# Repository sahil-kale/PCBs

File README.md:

# PCBs

Collection of PCB's designed for personal projects.<br/>
- Schematic and PCB designed in KiCAD

Currently working on: https://github.com/sahil-kale/PCBs/tree/main/PWM_Generator_KiCAD

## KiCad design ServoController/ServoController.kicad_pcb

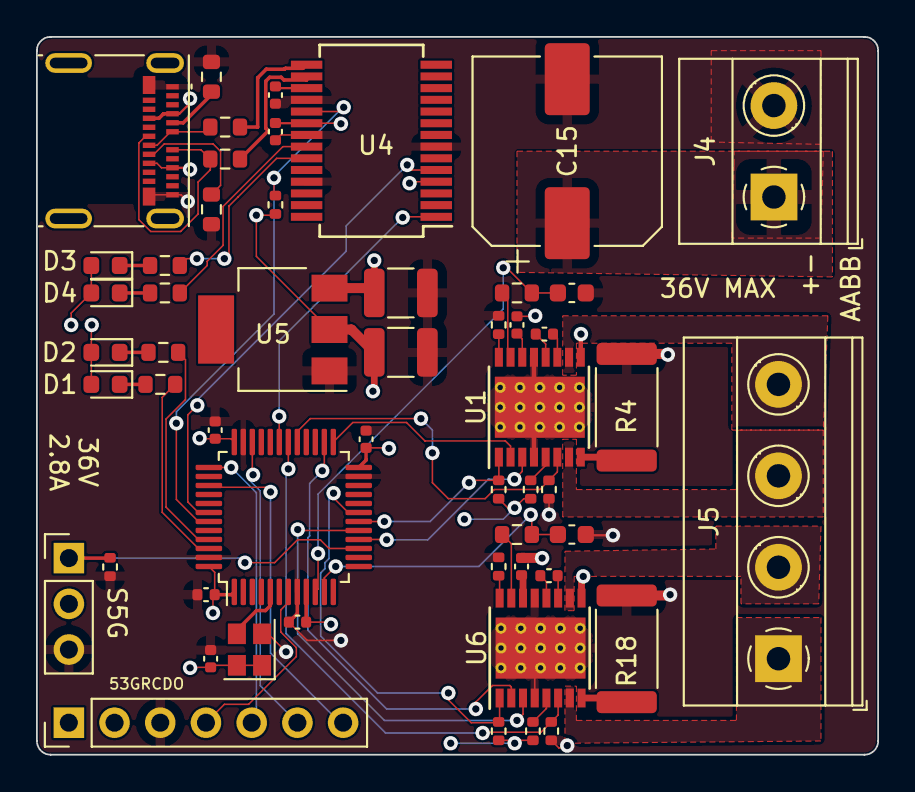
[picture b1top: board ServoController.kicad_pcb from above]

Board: 4 copper layers, 46.7 x 39.9 mm, 53 parts (0 on the bottom side), 56 nets.

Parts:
C1, C2, C13, C14: 0.1uF X7R; C_0402_1005Metric
C3, C4, C5, C6, C7, C8, C11: 0.1uF; C_0402_1005Metric
C9, C10: 22uF; C_1210_3225Metric
C15: 100uF; CP_Elec_10x10
C16, C17: 1000pF; C_0603_1608Metric
D1, D2, D3, D4: LED; LED_0603_1608Metric
J1: Conn_01x03; PinHeader_1x03_P2.54mm_Vertical
J2: Conn_01x07; PinHeader_1x07_P2.54mm_Vertical
J3: USB_C_Receptacle_USB2.0; USB_C_Receptacle_Molex_105450-0101
J4: Conn_01x02; TerminalBlock_Phoenix_MKDS-1,5-2-5.08_1x02_P5.08mm_Horizont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
J5: Conn_01x04; TerminalBlock_Phoenix_MKDS-1,5-4-5.08_1x04_P5.08mm_Horizont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
R1, R2, R3, R5, R12, R15, R16, R17, R19, R20: 10k; R_0402_1005Metric
R4, R18: 200m; R_2512_6332Metric
R6, R7, R13, R14: 470; R_0603_1608Metric
R8, R9: 5.1k; R_0603_1608Metric
R10, R11: 22R; R_0603_1608Metric
R21, R22: 100k; R_0603_1608Metric
U1, U6: DRV8801PWP; HTSSOP-16-1EP_4.4x5mm_P0.65mm_EP3.4x5mm_Mask3x3mm_ThermalVi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
U2: SG-8101CG 40MHz TCHSA; Crystal_SMD_2520-4Pin_2.5x2.0mm
U3: STM32L431CCTx; LQFP-48_7x7mm_P0.5mm
U4: FT232RL; SSOP-28_5.3x10.2mm_P0.65mm
U5: AZ1117-3.3; SOT-223

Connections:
+3V3: C3.1, C4.1, C5.1, C6.1, C7.1, C10.1, D1.2 (A), D2.2 (A), J2.2, R1.1, R5.1, R12.1, R15.1, R19.1, U2.1 (INH), U2.4 (VCC), U3.1 (VBAT), U3.9 (VDDA), U3.24 (VDD), U3.36 (VDD), U3.48 (VDD), U4.4 (VCCIO), U5.2 (VO)
+5V: C9.1, C11.1, D3.2 (A), D4.2 (A), J1.2, J2.1, J3.A4 (VBUS), J3.A9 (VBUS), J3.B4 (VBUS), J3.B9 (VBUS), U4.20 (VCC), U5.3 (VI)
/HBridge1/BRAKE: U3.26 (PB13), U6.2 (MODE1)
/HBridge1/CURR: C17.1, R22.2, U3.11 (PA1)
/HBridge1/DIR: U3.17 (PA7), U6.3 (PHASE)
/HBridge1/EN: R16.1, U3.30 (PA9), U6.6 (ENABLE)
/HBridge1/FAULT: R19.2, U3.19 (PB1), U6.1 (~FAULT)
/HBridge1/OUT+: J5.1, U6.7 (OUT+)
/HBridge1/OUT-: J5.2, U6.10 (OUT-)
/HBridge1/SLEEP: R15.2, U6.5 (~SLEEP)
/HBridge/BRAKE: U1.2 (MODE1), U3.25 (PB12)
/HBridge/CURR: C16.1, R21.2, U3.10 (PA0)
/HBridge/DIR: U1.3 (PHASE), U3.16 (PA6)
/HBridge/EN: R2.1, U1.6 (ENABLE), U3.29 (PA8)
/HBridge/FAULT: R5.2, U1.1 (~FAULT), U3.18 (PB0)
/HBridge/OUT+: J5.3, U1.7 (OUT+)
/HBridge/OUT-: J5.4, U1.10 (OUT-)
/HBridge/SLEEP: R1.2, U1.5 (~SLEEP)
/MCU/NRST: J2.4, U3.7 (NRST)
/MCU/PWM_IN: J1.1, R20.1, U3.15 (PA5)
/MCU/RX: U3.31 (PA10), U4.1 (TXD)
/MCU/SWCLK: J2.5, U3.37 (PA14)
/MCU/SWDIO: J2.6, U3.34 (PA13)
/MCU/SWO: J2.7, U3.39 (PB3)
/MCU/TX: U3.42 (PB6), U4.5 (RXD)
/MCU/UART_RESET: R12.2, U3.43 (PB7), U4.19 (~RESET)
/USB/D+: R11.2, U4.15 (USBD+)
/USB/D-: R10.2, U4.16 (USBD-)
/USB/DN: J3.A7 (D-), J3.B7 (D-), R10.1
/USB/DP: J3.A6 (D+), J3.B6 (D+), R11.1
/USBUART/RXLED: R14.2, U4.22 (CBUS1)
/USBUART/TXLED: R13.2, U4.23 (CBUS0)
GND: C3.2, C4.2, C5.2, C6.2, C7.2, C8.2, C9.2, C10.2, C11.2, C15.2, C16.2, C17.2, J1.3, J2.3, J3.A1 (GND), J3.A12 (GND), J3.B1 (GND), J3.B12 (GND), J4.2, R2.2, R3.2, R4.2, R8.2, R9.2, R16.2, R17.2, R18.2, R20.2, U1.4 (GND), U1.13 (GND), U1.17 (GND(PPAD)), U2.2 (GND), U3.8 (VSSA), U3.23 (VSS), U3.35 (VSS), U3.47 (VSS), U4.7 (GND), U4.18 (GND), U4.21 (GND), U4.25 (AGND), U5.1 (GND), U6.4 (GND), U6.13 (GND), U6.17 (GND(PPAD))
unnamed: C1.1, U1.12 (CP2)
unnamed: C1.2, U1.11 (CP1)
unnamed: C2.1, U1.14 (VCP)
unnamed: C8.1, U4.17 (3V3OUT)
unnamed: C13.1, U6.12 (CP2)
unnamed: C13.2, U6.11 (CP1)
unnamed: C14.1, U6.14 (VCP)
unnamed: D1.1 (K), R6.2
unnamed: D2.1 (K), R7.2
unnamed: D3.1 (K), R13.1
unnamed: D4.1 (K), R14.1
unnamed: J3.A5 (CC1), R9.1
unnamed: J3.B5 (CC2), R8.1
unnamed: R3.1, U1.16 (MODE2)
unnamed: R4.1, U1.8 (SENSE)
unnamed: R6.1, U3.46 (PB9)
unnamed: R7.1, U3.45 (PB8)
unnamed: R17.1, U6.16 (MODE2)
unnamed: R18.1, U6.8 (SENSE)
unnamed: R21.1, U1.15 (VPROPI)
unnamed: R22.1, U6.15 (VPROPI)
unnamed: U2.3 (CLK), U3.5 (PH0)
VBUS: C2.2, C14.2, C15.1, J4.1, U1.9 (VBB), U6.9 (VBB)

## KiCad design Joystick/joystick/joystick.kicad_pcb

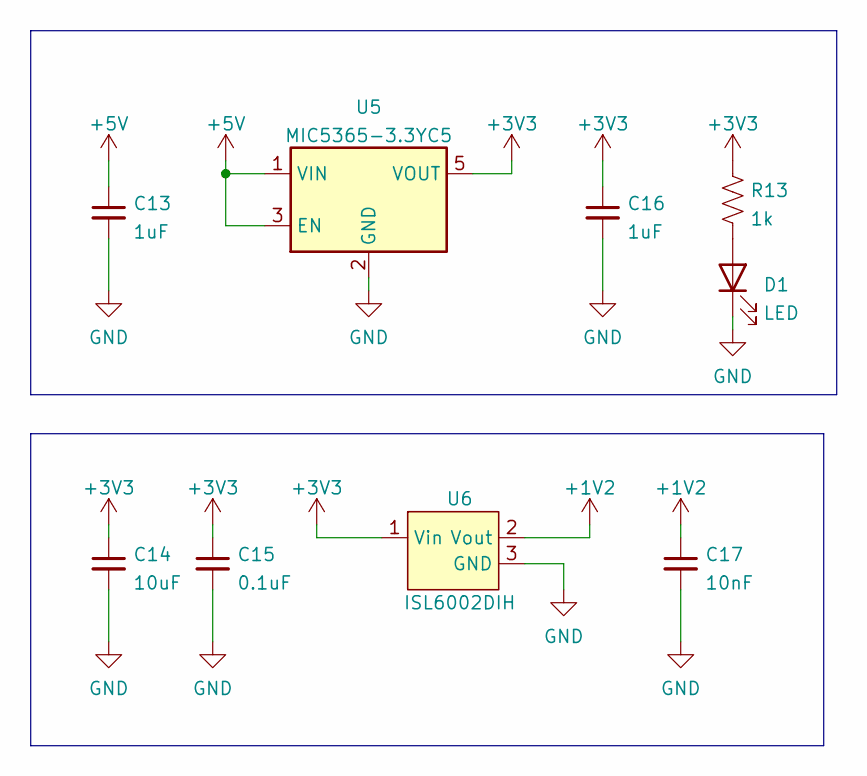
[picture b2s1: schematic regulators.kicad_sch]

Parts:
C13, C16: 1uF; C_0603_1608Metric_Pad1.08x0.95mm_HandSolder; Digikey Part Number 1276-1102-1-ND
C14: 10uF; C_0603_1608Metric_Pad1.08x0.95mm_HandSolder; Digikey Part Number 1276-1119-1-ND
C15: 0.1uF; C_0603_1608Metric_Pad1.08x0.95mm_HandSolder; Digikey Part Number 1276-CL10B104KB8NNNLCT-ND
C17: 10nF; C_0603_1608Metric_Pad1.08x0.95mm_HandSolder; Digikey Part Number 1292-1386-1-ND
D1: LED; LED_0603_1608Metric_Pad1.05x0.95mm_HandSolder; Digikey Part Number 3147-B1931UYG-20D000314U1930CT-ND
R13: 1k; R_0603_1608Metric_Pad0.98x0.95mm_HandSolder; Digikey Part Number RNCP0603FTD1K00CT-ND
U5: MIC5365-3.3YC5; SOT-353_SC-70-5; Digikey Part Number 576-3215-1-ND
U6: ISL6002DIH; SOT-23; Digikey Part Number ISL60002DIH311Z-TKCT-ND

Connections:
+1V2: C17.1, U6.2 (Vout); also elsewhere on the board
+3V3: C14.1, C15.1, C16.1, R13.1, U5.5 (VOUT), U6.1 (Vin); also elsewhere on the board
+5V: C13.1, U5.1 (VIN), U5.3 (EN); also elsewhere on the board
GND: C13.2, C14.2, C15.2, C16.2, C17.2, D1.1 (K), U5.2 (GND), U6.3 (GND); also elsewhere on the board
unnamed: D1.2 (A), R13.2

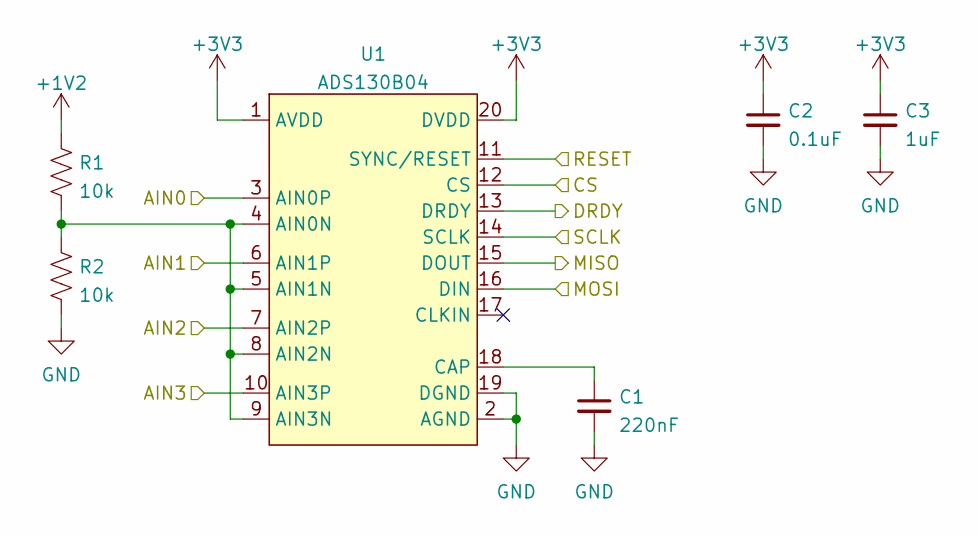
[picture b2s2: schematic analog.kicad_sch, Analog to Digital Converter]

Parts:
C1: 220nF; C_0603_1608Metric_Pad1.08x0.95mm_HandSolder; Digikey Part Number 1292-1419-1-ND
C2: 0.1uF; C_0603_1608Metric_Pad1.08x0.95mm_HandSolder; Digikey Part Number 1276-CL10B104KB8NNNLCT-ND
C3: 1uF; C_0603_1608Metric_Pad1.08x0.95mm_HandSolder; Digikey Part Number 1276-1102-1-ND
R1, R2: 10k; R_0603_1608Metric_Pad0.98x0.95mm_HandSolder; Digikey Part Number RNCP0603FTD10K0CT-ND
U1: ADS130B04; TSSOP-20_4.4x6.5mm_P0.65mm; Digikey Part Number 296-ADS130B04QPWRQ1CT-ND

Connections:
+1V2: R1.1; also elsewhere on the board
+3V3: C2.1, C3.1, U1.1 (AVDD), U1.20 (DVDD); also elsewhere on the board
/Analog Interfaces/AIN0: U1.3 (AIN0P); also elsewhere on the board
/Analog Interfaces/AIN1: U1.6 (AIN1P); also elsewhere on the board
/Analog Interfaces/AIN2: U1.7 (AIN2P); also elsewhere on the board
/Analog Interfaces/AIN3: U1.10 (AIN3P); also elsewhere on the board
/Analog Interfaces/CS: U1.12 (CS); also elsewhere on the board
/Analog Interfaces/DRDY: U1.13 (DRDY); also elsewhere on the board
/Analog Interfaces/MISO: U1.15 (DOUT); also elsewhere on the board
/Analog Interfaces/MOSI: U1.16 (DIN); also elsewhere on the board
/Analog Interfaces/RESET: U1.11 (SYNC/RESET); also elsewhere on the board
/Analog Interfaces/SCLK: U1.14 (SCLK); also elsewhere on the board
GND: C1.2, C2.2, C3.2, R2.2, U1.2 (AGND), U1.19 (DGND); also elsewhere on the board
unnamed: C1.1, U1.18 (CAP)
unnamed: R1.2, R2.1, U1.4 (AIN0N), U1.5 (AIN1N), U1.8 (AIN2N), U1.9 (AIN3N)

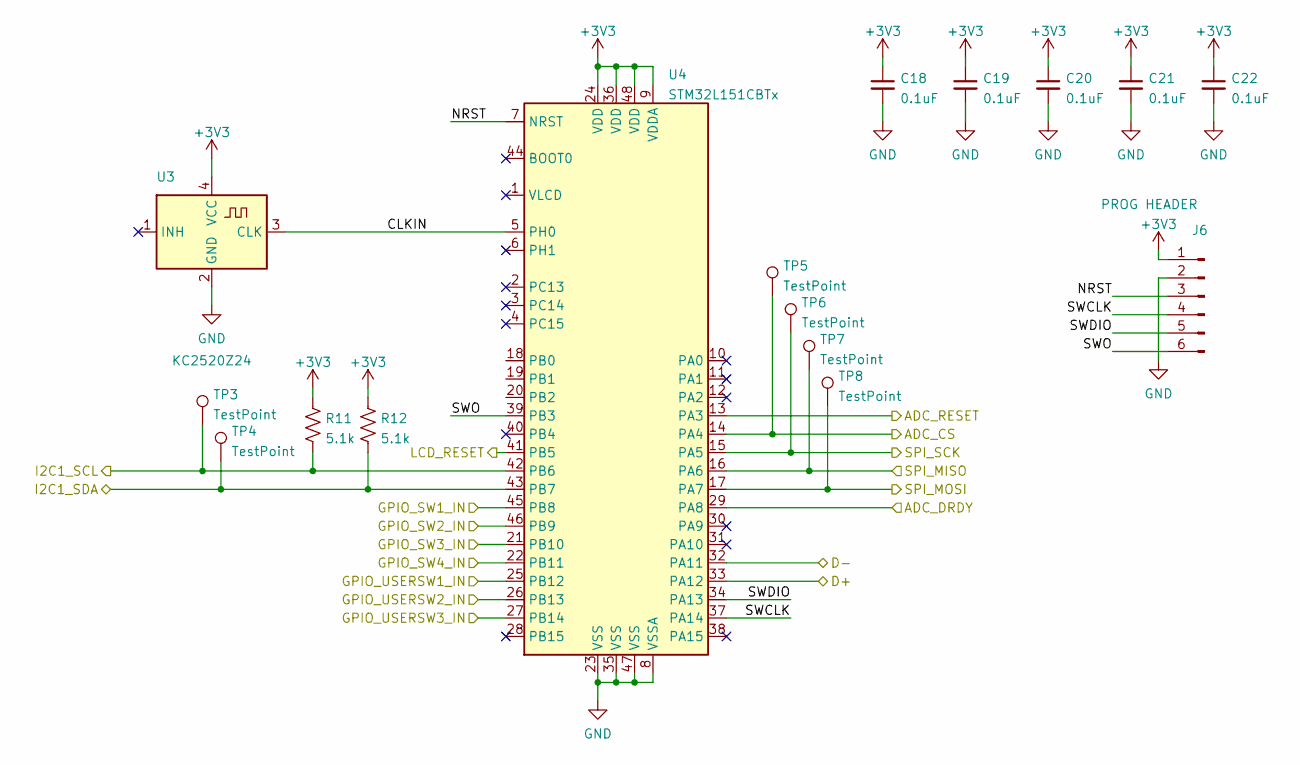
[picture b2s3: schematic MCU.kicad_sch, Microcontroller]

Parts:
C18, C19, C20, C21, C22: 0.1uF; C_0603_1608Metric_Pad1.08x0.95mm_HandSolder
J6: PROG HEADER; PinHeader_1x06_P2.54mm_Vertical
R11, R12: 5.1k; R_0603_1608Metric_Pad0.98x0.95mm_HandSolder; Digikey Part Number RMCF0603JT5K10CT-ND
TP3, TP4, TP5, TP6, TP7, TP8: TestPoint; TestPoint_Pad_D1.0mm
U3: KC2520Z24; Oscillator_SMD_Kyocera_KC2520Z-4Pin_2.5x2.0mm; Digikey Part Number 478-KC2520Z24.0000C15XXKCT-ND
U4: STM32L151CBTx; LQFP-48_7x7mm_P0.5mm; Digikey Part Number 497-11191-ND

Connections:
+3V3: C18.1, C19.1, C20.1, C21.1, C22.1, J6.1, R11.1, R12.1, U3.4 (VCC), U4.9 (VDDA), U4.24 (VDD), U4.36 (VDD), U4.48 (VDD); also elsewhere on the board
/Analog Interfaces/CS: TP5.1, U4.14 (PA4); also elsewhere on the board
/Analog Interfaces/DRDY: U4.29 (PA8); also elsewhere on the board
/Analog Interfaces/MISO: TP7.1, U4.16 (PA6); also elsewhere on the board
/Analog Interfaces/MOSI: TP8.1, U4.17 (PA7); also elsewhere on the board
/Analog Interfaces/RESET: U4.13 (PA3); also elsewhere on the board
/Analog Interfaces/SCLK: TP6.1, U4.15 (PA5); also elsewhere on the board
/Button Interfaces/SW_1: U4.45 (PB8); also elsewhere on the board
/Button Interfaces/SW_2: U4.46 (PB9); also elsewhere on the board
/Button Interfaces/SW_3: U4.21 (PB10); also elsewhere on the board
/Button Interfaces/SW_4: U4.22 (PB11); also elsewhere on the board
/Button Interfaces/USER_SW_1: U4.25 (PB12); also elsewhere on the board
/Button Interfaces/USER_SW_2: U4.26 (PB13); also elsewhere on the board
/Button Interfaces/USER_SW_3: U4.27 (PB14); also elsewhere on the board
/LCD/RST: U4.41 (PB5); also elsewhere on the board
/LCD/SCL: R11.2, TP3.1, U4.42 (PB6); also elsewhere on the board
/LCD/SDA: R12.2, TP4.1, U4.43 (PB7); also elsewhere on the board
/MCU/CLKIN: U3.3 (CLK), U4.5 (PH0)
/MCU/NRST: J6.3, U4.7 (NRST)
/MCU/SWCLK: J6.4, U4.37 (PA14)
/MCU/SWDIO: J6.5, U4.34 (PA13)
/MCU/SWO: J6.6, U4.39 (PB3)
/USB/D+: U4.33 (PA12); also elsewhere on the board
/USB/D-: U4.32 (PA11); also elsewhere on the board
GND: C18.2, C19.2, C20.2, C21.2, C22.2, J6.2, U3.2 (GND), U4.8 (VSSA), U4.23 (VSS), U4.35 (VSS), U4.47 (VSS); also elsewhere on the board

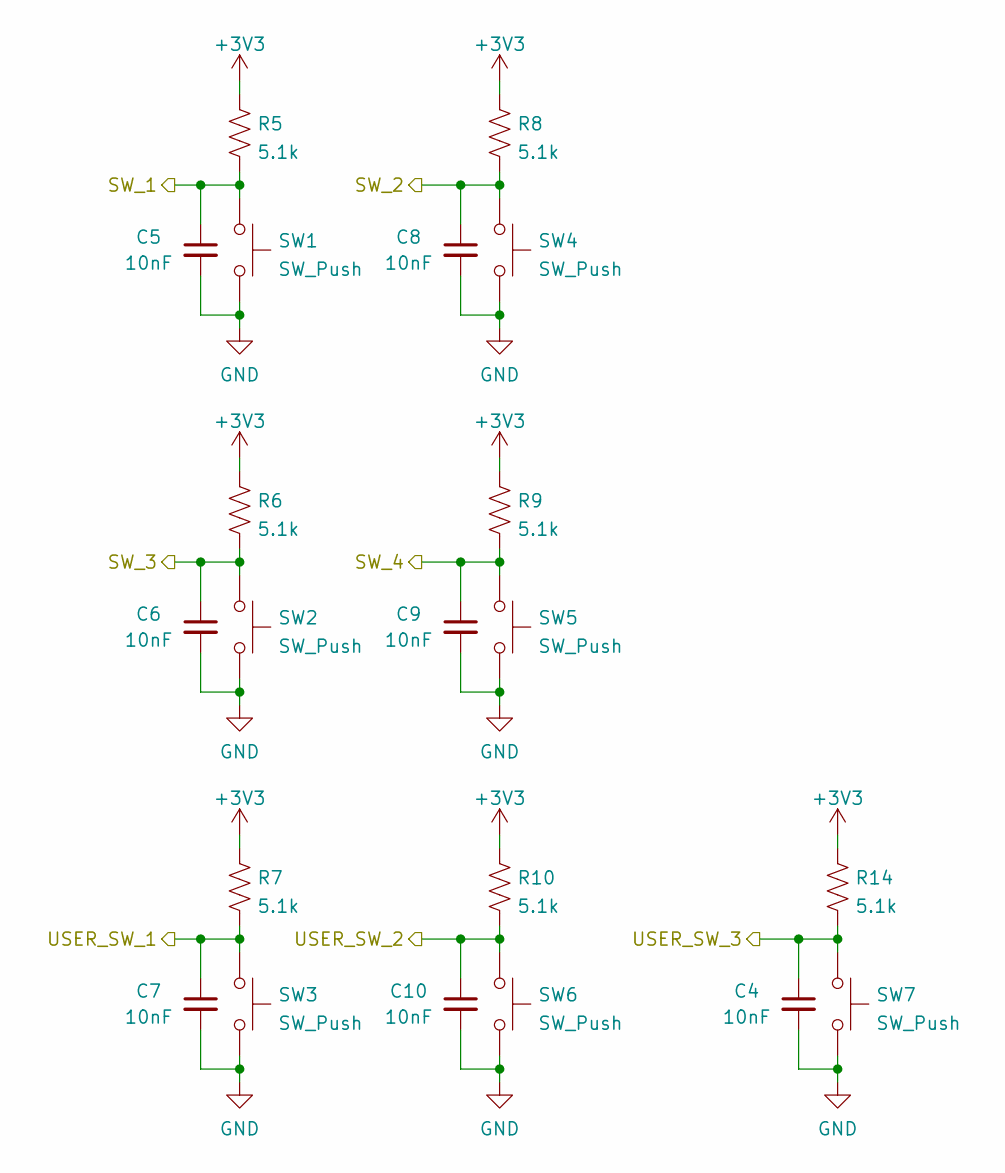
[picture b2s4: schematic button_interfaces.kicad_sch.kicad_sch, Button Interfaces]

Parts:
C4, C5, C6, C7, C8, C9, C10: 10nF; C_0603_1608Metric_Pad1.08x0.95mm_HandSolder; Digikey Part Number 1292-1386-1-ND
R5, R6, R7, R8, R9, R10, R14: 5.1k; R_0603_1608Metric_Pad0.98x0.95mm_HandSolder; Digikey Part Number RMCF0603JT5K10CT-ND
SW1, SW2, SW3, SW4, SW5, SW6, SW7: SW_Push; SW_Push_1P1T_NO_6x6mm_H9.5mm; Digikey Part Number 360-2595-1-ND

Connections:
+3V3: R5.1, R6.1, R7.1, R8.1, R9.1, R10.1, R14.1; also elsewhere on the board
/Button Interfaces/SW_1: C5.1, R5.2, SW1.1; also elsewhere on the board
/Button Interfaces/SW_2: C8.1, R8.2, SW4.1; also elsewhere on the board
/Button Interfaces/SW_3: C6.1, R6.2, SW2.1; also elsewhere on the board
/Button Interfaces/SW_4: C9.1, R9.2, SW5.1; also elsewhere on the board
/Button Interfaces/USER_SW_1: C7.1, R7.2, SW3.1; also elsewhere on the board
/Button Interfaces/USER_SW_2: C10.1, R10.2, SW6.1; also elsewhere on the board
/Button Interfaces/USER_SW_3: C4.1, R14.2, SW7.1; also elsewhere on the board
GND: C4.2, C5.2, C6.2, C7.2, C8.2, C9.2, C10.2, SW1.2, SW2.2, SW3.2, SW4.2, SW5.2, SW6.2, SW7.2; also elsewhere on the board

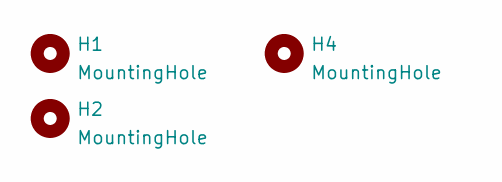
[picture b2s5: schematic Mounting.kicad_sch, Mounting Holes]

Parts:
H1, H2, H4: MountingHole; MountingHole_2.1mm

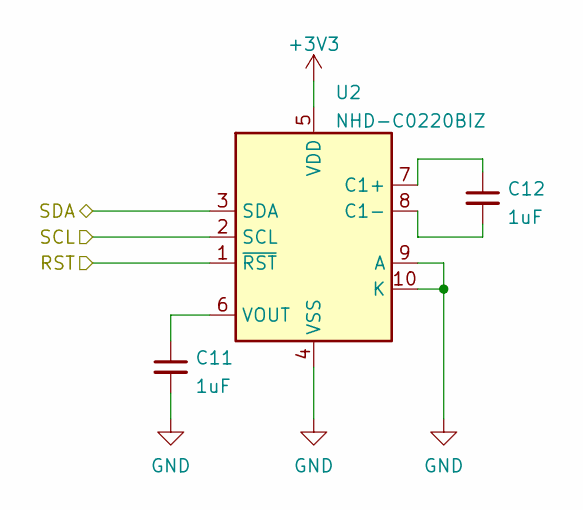
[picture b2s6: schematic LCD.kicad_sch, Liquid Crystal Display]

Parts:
C11, C12: 1uF; C_0603_1608Metric_Pad1.08x0.95mm_HandSolder; Digikey Part Number 1276-1102-1-ND
U2: NHD-C0220BIZ; NHD-C0220BiZ; Digikey Part Number NHD-C0220BIZ-FSW-FBW-3V3M-ND

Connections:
+3V3: U2.5 (VDD); also elsewhere on the board
/LCD/RST: U2.1 (~RST); also elsewhere on the board
/LCD/SCL: U2.2 (SCL); also elsewhere on the board
/LCD/SDA: U2.3 (SDA); also elsewhere on the board
GND: C11.2, U2.4 (VSS), U2.9 (A), U2.10 (K); also elsewhere on the board
unnamed: C11.1, U2.6 (VOUT)
unnamed: C12.1, U2.7 (C1+)
unnamed: C12.2, U2.8 (C1-)

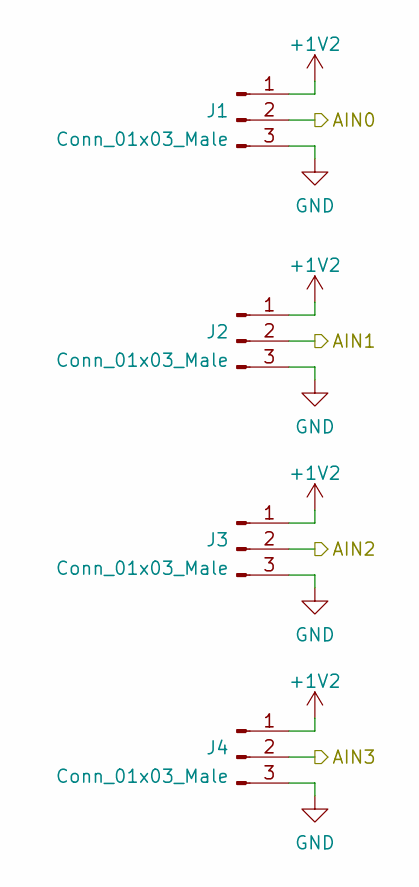
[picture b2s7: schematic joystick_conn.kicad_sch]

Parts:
J1, J2, J3, J4: Conn_01x03_Male; PinHeader_1x03_P2.54mm_Vertical

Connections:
+1V2: J1.1, J2.1, J3.1, J4.1; also elsewhere on the board
/Analog Interfaces/AIN0: J1.2; also elsewhere on the board
/Analog Interfaces/AIN1: J2.2; also elsewhere on the board
/Analog Interfaces/AIN2: J3.2; also elsewhere on the board
/Analog Interfaces/AIN3: J4.2; also elsewhere on the board
GND: J1.3, J2.3, J3.3, J4.3; also elsewhere on the board

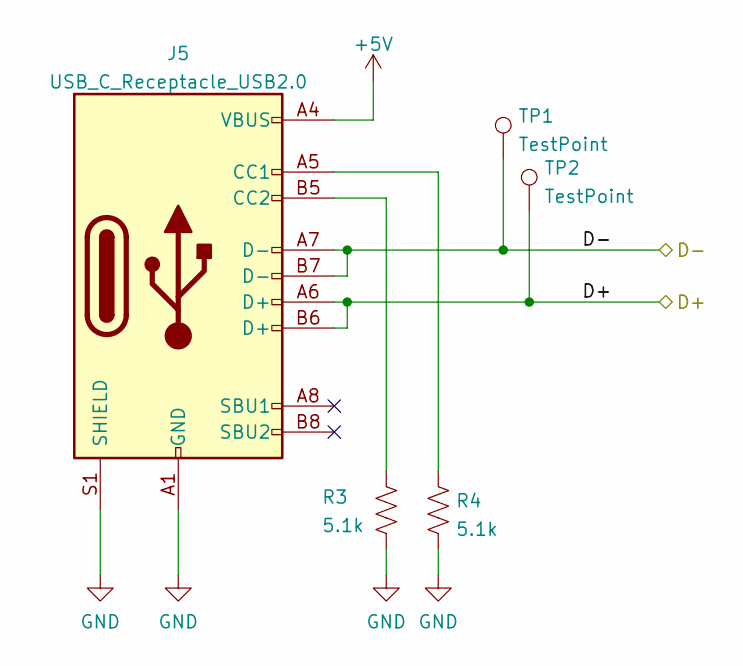
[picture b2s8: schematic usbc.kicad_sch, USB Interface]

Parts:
J5: USB_C_Receptacle_USB2.0; USB_C_Receptacle_JAE_DX07S016JA1R1500; Digikey Part Number 670-DX07S016JA1R1500CT-ND
R3, R4: 5.1k; R_0603_1608Metric_Pad0.98x0.95mm_HandSolder; Digikey Part Number RMCF0603JT5K10CT-ND
TP1, TP2: TestPoint; TestPoint_Pad_D1.0mm

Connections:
+5V: J5.A4 (VBUS), J5.A9 (VBUS), J5.B4 (VBUS), J5.B9 (VBUS); also elsewhere on the board
/USB/D+: J5.A6 (D+), J5.B6 (D+), TP2.1; also elsewhere on the board
/USB/D-: J5.A7 (D-), J5.B7 (D-), TP1.1; also elsewhere on the board
GND: J5.A1 (GND), J5.A12 (GND), J5.B1 (GND), J5.B12 (GND), J5.S1 (SHIELD), R3.2, R4.2; also elsewhere on the board
unnamed: J5.A5 (CC1), R4.1
unnamed: J5.B5 (CC2), R3.1

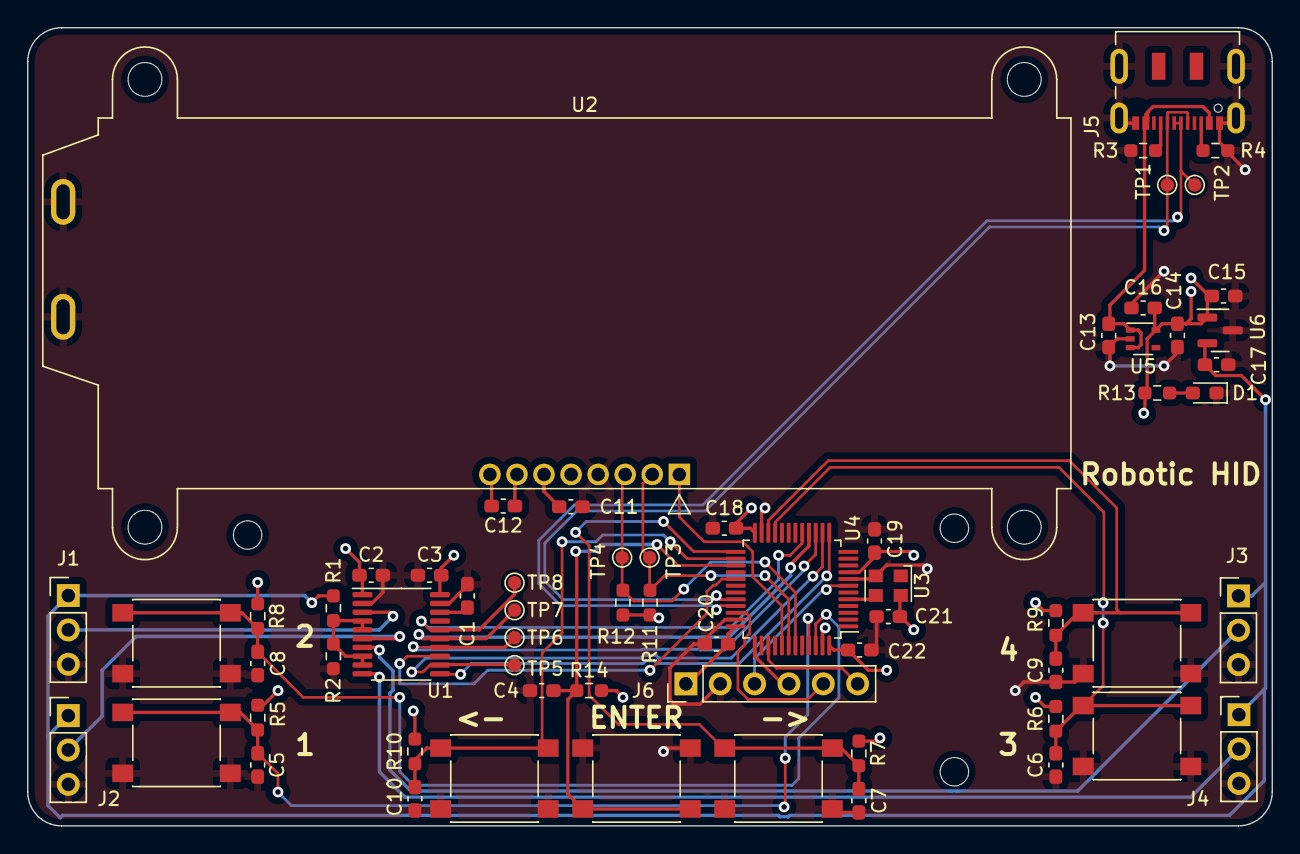
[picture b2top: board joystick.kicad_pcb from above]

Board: 4 copper layers, 92.0 x 59.0 mm, 67 parts (0 on the bottom side), 39 nets.

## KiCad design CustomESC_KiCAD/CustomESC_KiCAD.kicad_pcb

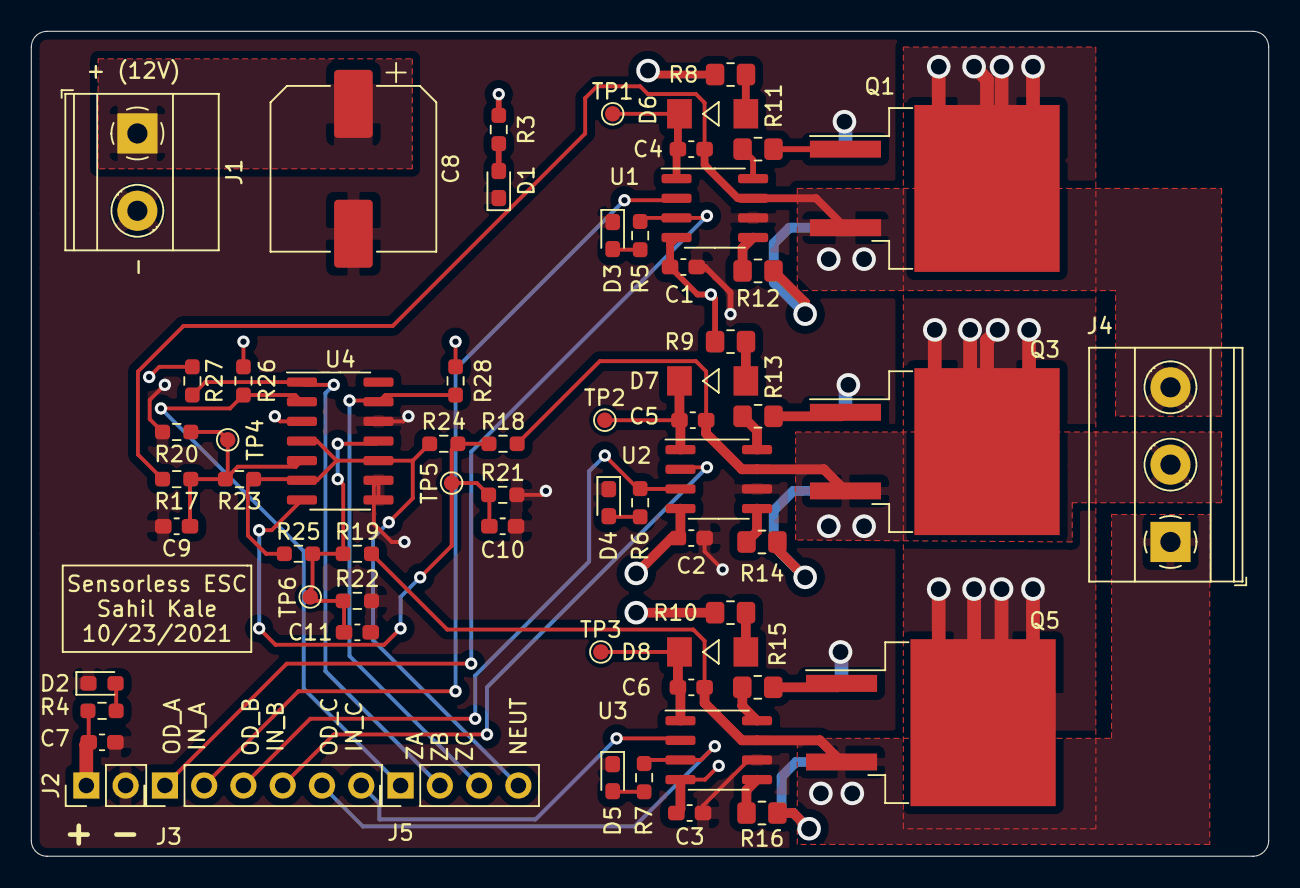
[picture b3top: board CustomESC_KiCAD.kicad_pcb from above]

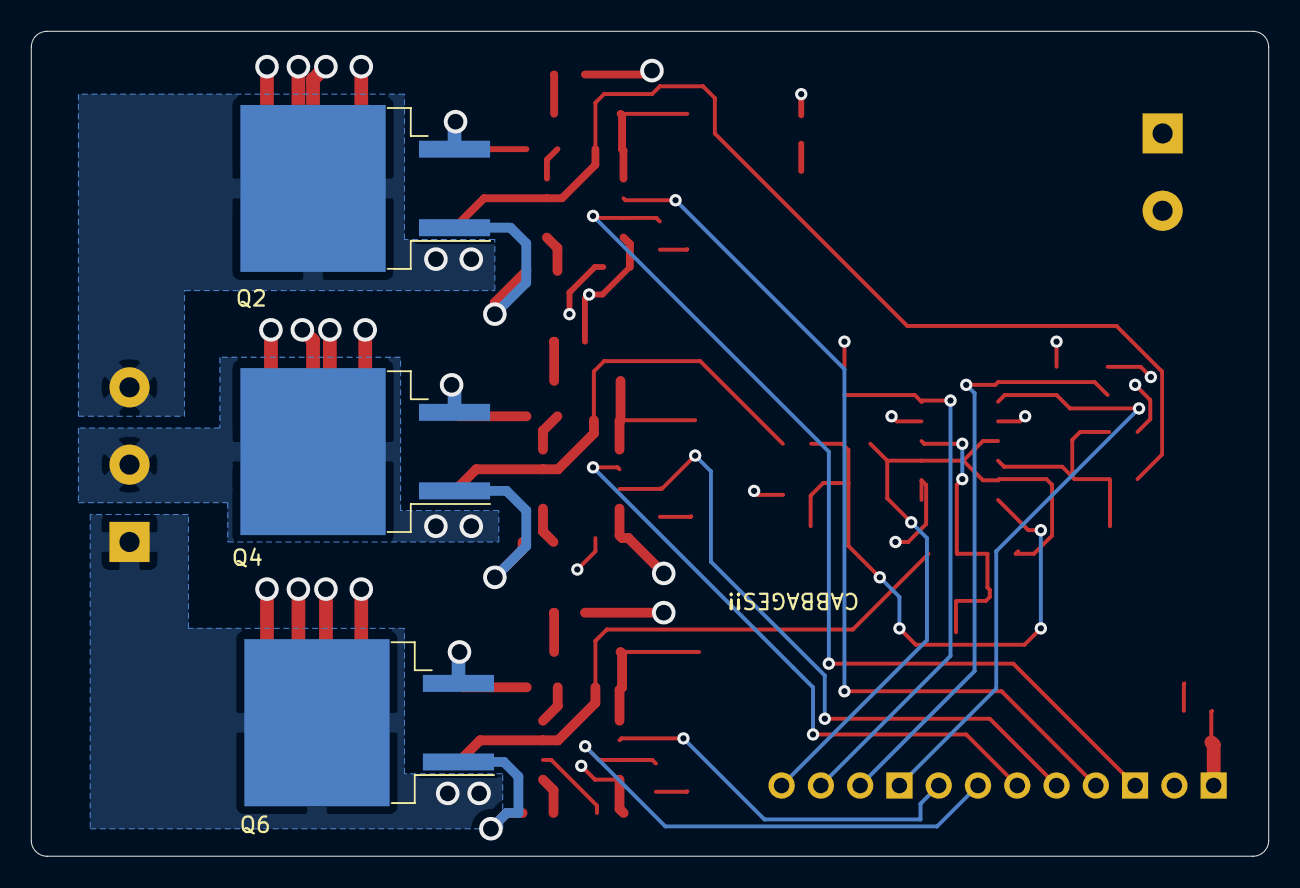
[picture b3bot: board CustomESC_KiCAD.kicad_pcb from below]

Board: 4 copper layers, 80.0 x 53.3 mm, 66 parts (3 on the bottom side), 42 nets.

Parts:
C1, C2, C3: 1uF; C_0603_1608Metric_Pad1.08x0.95mm_HandSolder
C4, C5, C6, C7: 0.1uF; C_0603_1608Metric_Pad1.08x0.95mm_HandSolder
C8: 100uF; CP_Elec_10x10.5
C9, C10, C11: 1nF; C_0603_1608Metric_Pad1.08x0.95mm_HandSolder
D1, D2, D3, D4, D5: LED; LED_0603_1608Metric_Pad1.05x0.95mm_HandSolder
D6, D7, D8: SK53AFL-TP; SK53AFL
J1: Screw_Terminal_01x02; TerminalBlock_Phoenix_MKDS-1,5-2_1x02_P5.00mm_Horizontal
J2: Screw_Terminal_01x02; PinHeader_1x02_P2.54mm_Vertical
J3: Screw_Terminal_01x06; PinHeader_1x06_P2.54mm_Vertical
J4: Screw_Terminal_01x03; TerminalBlock_Phoenix_MKDS-1,5-3_1x03_P5.00mm_Horizontal
J5: Screw_Terminal_01x04; PinHeader_1x04_P2.54mm_Vertical
Q1, Q2, Q3, Q4, Q5, Q6: Q_NMOS_GDS; TO-263-2
R3, R4, R5, R6, R7: 1k; R_0603_1608Metric_Pad0.98x0.95mm_HandSolder
R8, R9, R10, R11, R12, R13, R14, R15, R16: 5.1; R_0805_2012Metric_Pad1.20x1.40mm_HandSolder
R17, R18, R19, R23, R24, R25: 33k; R_0603_1608Metric_Pad0.98x0.95mm_HandSolder
R20, R21, R22, R26, R27, R28: 10k; R_0603_1608Metric_Pad0.98x0.95mm_HandSolder
TP1, TP2, TP3: TP_BST; TestPoint_Pad_D1.0mm
TP4, TP5, TP6: TestPoint; TestPoint_Pad_D1.0mm
U1, U2, U3: ADP3110AKRZ-RL; SOIC-8_3.9x4.9mm_P1.27mm
U4: LM339; SOIC-14_3.9x8.7mm_P1.27mm

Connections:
/BackEMF/BEMFA: C9.1, R17.1, R20.1, R23.2, TP4.1, U4.5
/BackEMF/BEMFB: C10.1, R18.1, R21.1, R24.2, TP5.1, U4.7
/BackEMF/BEMFC: C11.1, R19.1, R22.1, R25.2, TP6.1, U4.11
/IN_A: J3.2, U1.2
/IN_B: J3.4, U2.2
/IN_C: J3.6, U3.2
/OD_A: J3.1, R5.1, U1.3
/OD_B: J3.3, R6.1, U2.3
/OD_C: J3.5, R7.1, U3.3
GND: C1.2, C2.2, C3.2, C7.1, C8.2, C9.2, C10.2, C11.2, D1.1, D2.1, D3.1, D4.1, D5.1, J1.2, J2.2, Q2.3, Q4.3, Q6.3, R20.2, R21.2, R22.2, U1.6, U2.6, U3.6, U4.8, U4.9, U4.12
NEUT: J5.4, R23.1, R24.1, R25.1, U4.4, U4.6, U4.10
unnamed: C4.2, D6.1, TP1.1, U1.1
unnamed: C5.2, D7.1, TP2.1, U2.1
unnamed: C6.2, D8.1, TP3.1, U3.1
unnamed: D1.2, R3.2
unnamed: D2.2, R4.2
unnamed: D3.2, R5.2
unnamed: D4.2, R6.2
unnamed: D5.2, R7.2
unnamed: D6.2, R8.1
unnamed: D7.2, R9.1
unnamed: D8.2, R10.1
unnamed: Q1.1, R11.1
unnamed: Q2.1, R12.1
unnamed: Q3.1, R13.1
unnamed: Q4.1, R14.1
unnamed: Q5.1, R15.1
unnamed: Q6.1, R16.1
unnamed: R11.2, U1.8
unnamed: R12.2, U1.5
unnamed: R13.2, U2.8
unnamed: R14.2, U2.5
unnamed: R15.2, U3.8
unnamed: R16.2, U3.5
PHASEA: C4.1, J4.3, Q1.3, Q2.2, R17.2, U1.7
PHASEB: C5.1, J4.2, Q3.3, Q4.2, R18.2, U2.7
PHASEC: C6.1, J4.1, Q5.3, Q6.2, R19.2, U3.7
VBUS: C1.1, C2.1, C3.1, C8.1, J1.1, Q1.2, Q3.2, Q5.2, R3.1, R8.2, R9.2, R10.2, U1.4, U2.4, U3.4
VCC: C7.2, J2.1, R4.1, R26.1, R27.1, R28.1, U4.3
ZCROSS_A: J5.1, R26.2, U4.2
ZCROSS_B: J5.2, R27.2, U4.1
ZCROSS_C: J5.3, R28.2, U4.13

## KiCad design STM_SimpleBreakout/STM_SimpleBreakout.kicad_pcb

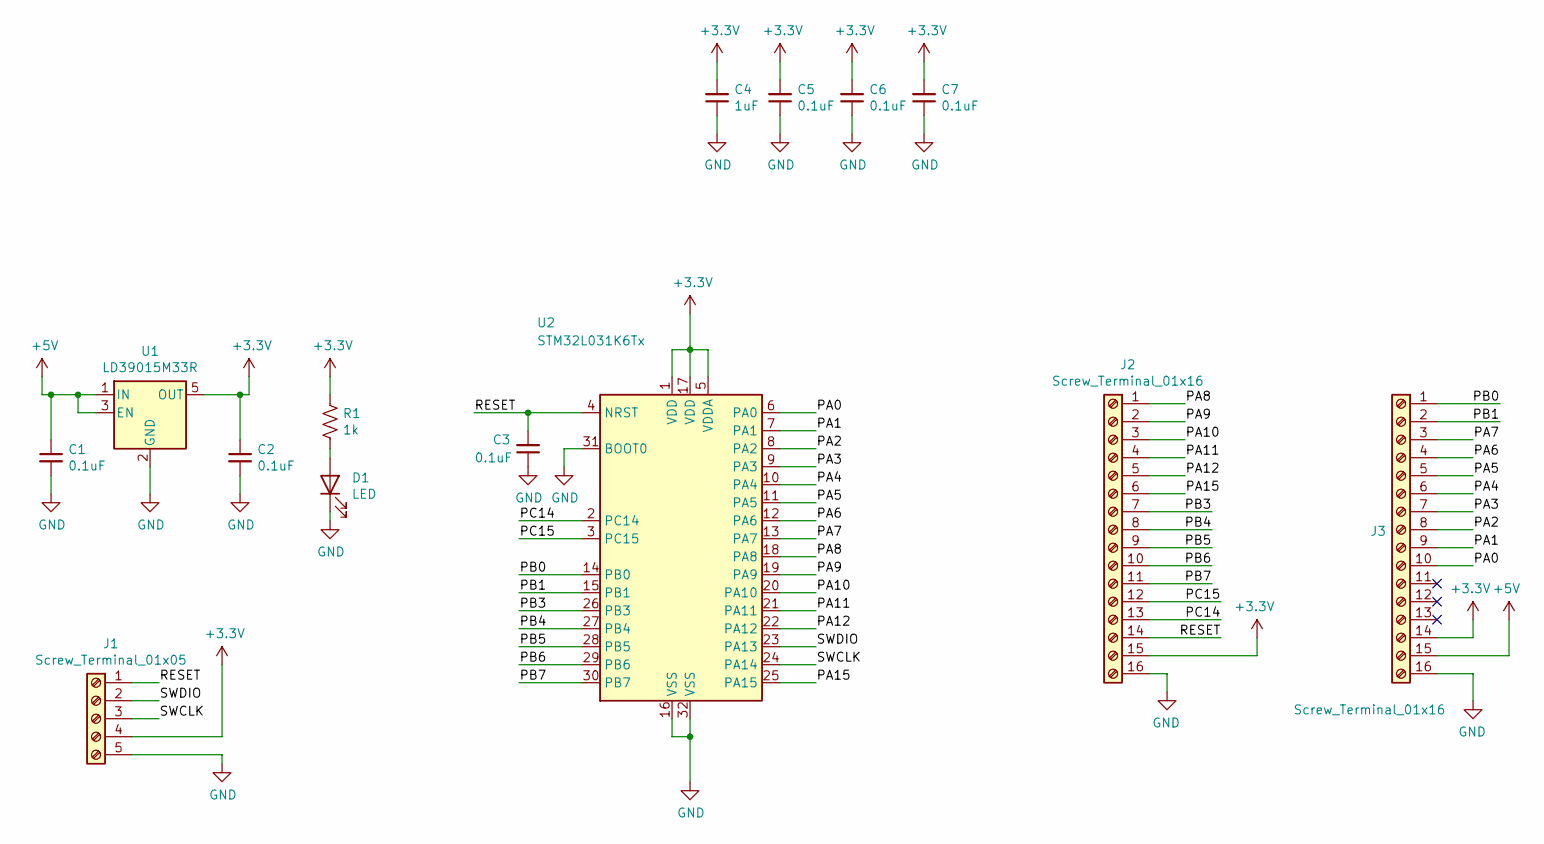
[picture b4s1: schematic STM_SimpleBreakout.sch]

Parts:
C1, C2, C3, C5, C6, C7: 0.1uF; C_0603_1608Metric_Pad1.08x0.95mm_HandSolder; Digikey Part Num 445-7435-1-ND
C4: 1uF; C_0603_1608Metric_Pad1.08x0.95mm_HandSolder; Digikey Part Num 445-7435-1-ND
D1: LED; LED_0603_1608Metric_Pad1.05x0.95mm_HandSolder
J1: Screw_Terminal_01x05; PinHeader_1x05_P2.54mm_Vertical
J2, J3: Screw_Terminal_01x16; PinHeader_1x16_P2.54mm_Vertical
R1: 1k; R_0603_1608Metric_Pad0.98x0.95mm_HandSolder
U1: LD39015M33R; SOT-23-5; Digikey Part Num 497-6979-1-ND
U2: STM32L031K6Tx; LQFP-32_7x7mm_P0.8mm; Digikey Part Num 497-18806-1-ND

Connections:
+3V3: C2.1, C4.2, C5.2, C6.2, C7.2, J1.4, J2.15, J3.14, R1.1, U1.5 (OUT), U2.1 (VDD), U2.5 (VDDA), U2.17 (VDD)
+5V: C1.1, J3.15, U1.1 (IN), U1.3 (EN)
/PA0: J3.10, U2.6 (PA0)
/PA1: J3.9, U2.7 (PA1)
/PA2: J3.8, U2.8 (PA2)
/PA3: J3.7, U2.9 (PA3)
/PA4: J3.6, U2.10 (PA4)
/PA5: J3.5, U2.11 (PA5)
/PA6: J3.4, U2.12 (PA6)
/PA7: J3.3, U2.13 (PA7)
/PA8: J2.1, U2.18 (PA8)
/PA9: J2.2, U2.19 (PA9)
/PA10: J2.3, U2.20 (PA10)
/PA11: J2.4, U2.21 (PA11)
/PA12: J2.5, U2.22 (PA12)
/PA15: J2.6, U2.25 (PA15)
/PB0: J3.1, U2.14 (PB0)
/PB1: J3.2, U2.15 (PB1)
/PB3: J2.7, U2.26 (PB3)
/PB4: J2.8, U2.27 (PB4)
/PB5: J2.9, U2.28 (PB5)
/PB6: J2.10, U2.29 (PB6)
/PB7: J2.11, U2.30 (PB7)
/PC14: J2.13, U2.2 (PC14)
/PC15: J2.12, U2.3 (PC15)
/RESET: C3.2, J1.1, J2.14, U2.4 (NRST)
/SWCLK: J1.3, U2.24 (PA14)
/SWDIO: J1.2, U2.23 (PA13)
GND: C1.2, C2.2, C3.1, C4.1, C5.1, C6.1, C7.1, D1.1 (K), J1.5, J2.16, J3.16, U1.2 (GND), U2.16 (VSS), U2.31 (BOOT0), U2.32 (VSS)
unnamed: D1.2 (A), R1.2

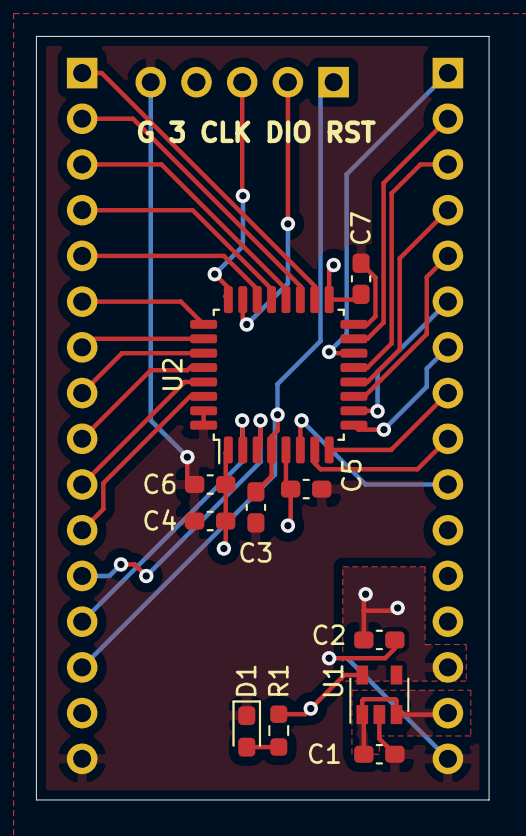
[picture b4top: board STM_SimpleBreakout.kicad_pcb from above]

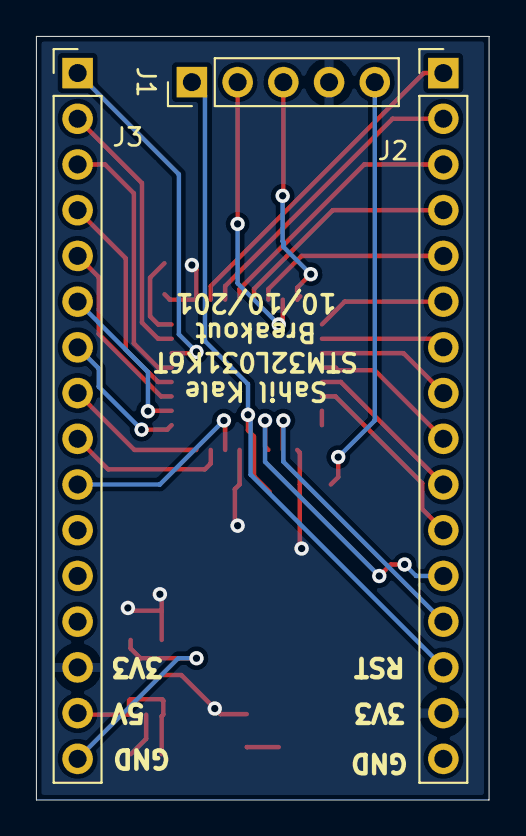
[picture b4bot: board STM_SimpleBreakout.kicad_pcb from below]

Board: 2 copper layers, 25.1 x 42.4 mm, 14 parts (3 on the bottom side), 30 nets.

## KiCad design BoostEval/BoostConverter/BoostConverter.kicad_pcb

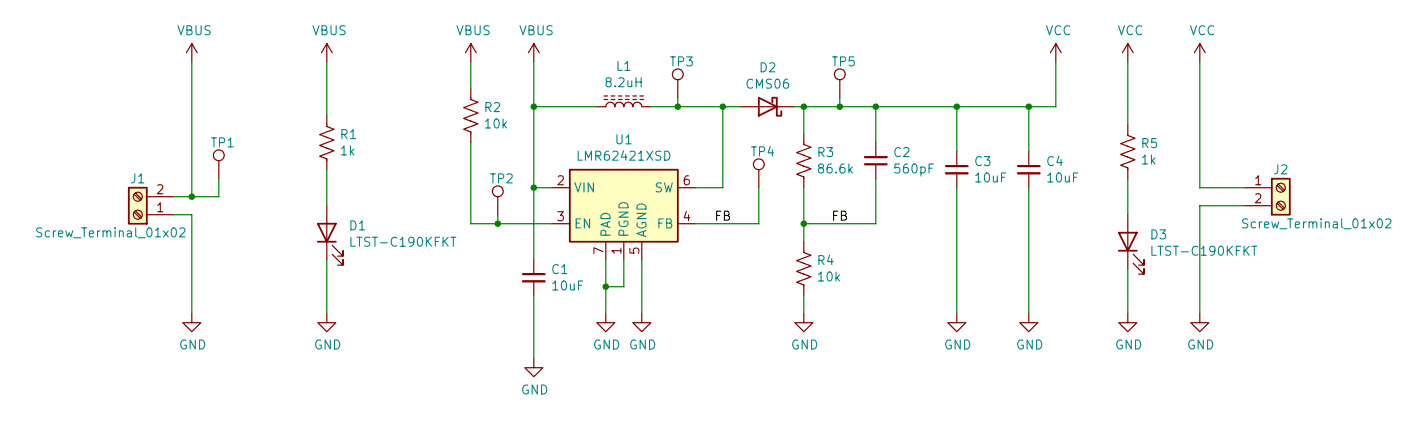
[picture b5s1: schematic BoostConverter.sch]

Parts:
C1, C3, C4: 10uF; C_0805_2012Metric_Pad1.18x1.45mm_HandSolder; Digikey Part Number 490-18663-1-ND
C2: 560pF; C_0603_1608Metric_Pad1.08x0.95mm_HandSolder; Digikey Part Number 1292-1454-1-ND
D1, D3: LTST-C190KFKT; LED_0603_1608Metric_Pad1.05x0.95mm_HandSolder; Digikey Part Number 160-1434-1-ND
D2: CMS06; Digikey Part Number CMS06QMCT-ND
J1, J2: Screw_Terminal_01x02; TerminalBlock_Phoenix_PT-1,5-2-5.0-H_1x02_P5.00mm_Horizontal; Digikey Part Number 277-1667-ND
L1: 8.2uH; SRN6045; Digikey Part Number SRN6045-8R2YCT-ND
R1, R5: 1k; R_0603_1608Metric_Pad0.98x0.95mm_HandSolder; Digikey Part Number RMCF0603FG1K00CT-ND
R2, R4: 10k; R_0603_1608Metric_Pad0.98x0.95mm_HandSolder; Digikey Part Number RMCF0603FT10K0CT-ND
R3: 86.6k; R_0603_1608Metric_Pad0.98x0.95mm_HandSolder; Digikey Part Number RMCF0603FT86K6CT-ND
TP1, TP2, TP3, TP4, TP5: TestPoint; TestPoint_Pad_D1.5mm
U1: LMR62421XSD; WSON-6-1EP_3x3mm_P0.95mm; Digikey Part Number 296-41447-1-ND

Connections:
/FB: C2.1, R3.2, R4.1, TP4.1, U1.4 (FB)
GND: C1.2, C3.2, C4.2, D1.1 (K), D3.1 (K), J1.1, J2.2, R4.2, U1.1 (PGND), U1.5 (AGND), U1.7 (PAD)
unnamed: D1.2 (A), R1.2
unnamed: D2.2 (A), L1.2, TP3.1, U1.6 (SW)
unnamed: D3.2 (A), R5.2
unnamed: R2.2, TP2.1, U1.3 (EN)
VBUS: C1.1, J1.2, L1.1, R1.1, R2.1, TP1.1, U1.2 (VIN)
VCC: C2.2, C3.1, C4.1, D2.1 (K), J2.1, R3.1, R5.1, TP5.1

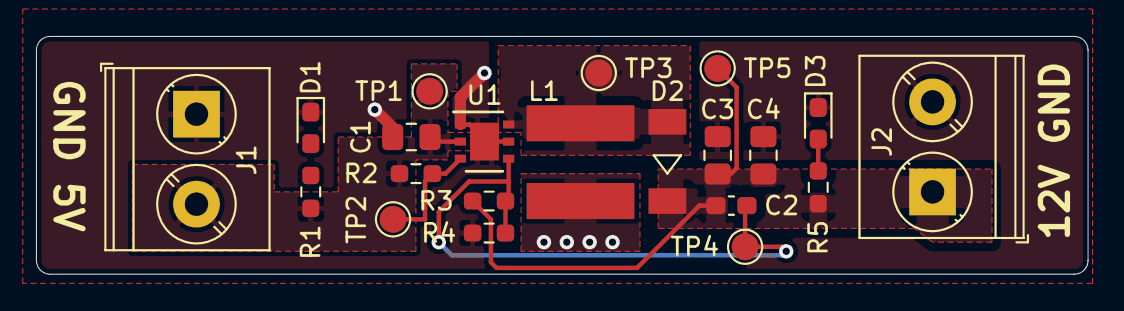
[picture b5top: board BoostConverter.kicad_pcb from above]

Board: 2 copper layers, 58.4 x 13.2 mm, 21 parts (0 on the bottom side), 8 nets.
